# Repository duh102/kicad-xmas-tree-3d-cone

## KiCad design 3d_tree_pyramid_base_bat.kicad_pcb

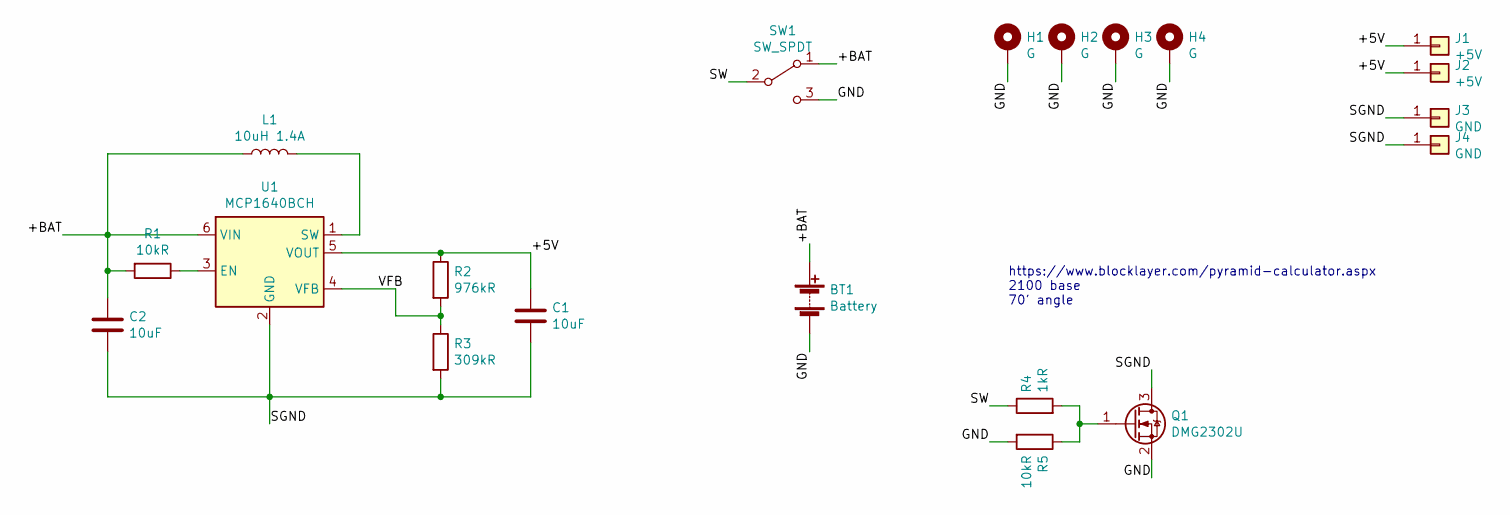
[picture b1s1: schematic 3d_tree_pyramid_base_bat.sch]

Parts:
BT1: Battery; BatteryHolder_Keystone_2479_3xAAA_noscrew
C1: 10uF; C_0805_2012Metric
C2: 10uF; C_0603_1608Metric
H1, H2, H3, H4: G; MountingHole_3.2mm_M3_DIN965_Pad
J1, J2: +5V; TestPoint_Pad_D2.0mm
J3, J4: GND; TestPoint_Pad_D2.0mm
L1: 10uH 1.4A; L_Taiyo-Yuden_NR-40xx
Q1: DMG2302U; SOT-23
R1, R5: 10kR; R_0805_2012Metric
R2: 976kR; R_0805_2012Metric
R3: 309kR; R_0805_2012Metric
R4: 1kR; R_0805_2012Metric
SW1: SW_SPDT; SW_Slide_1P2T_CK_OS102011MS2Q
U1: MCP1640BCH; SOT-23-6

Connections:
/+5V: C1.1, J1.1, J2.1, R2.1, U1.5 (VOUT)
/+BAT: BT1.1 (+), C2.1, L1.1, R1.2, SW1.1 (A), U1.6 (VIN)
/GND: BT1.2 (-), H1.1, H2.1, H3.1, H4.1, Q1.2 (S), R5.2, SW1.3 (C)
/SGND: C1.2, C2.2, J3.1, J4.1, Q1.3 (D), R3.2, U1.2 (GND)
/SW: R4.1, SW1.2 (B)
/VFB: R2.2, R3.1, U1.4 (VFB)
unnamed: L1.2, U1.1 (SW)
unnamed: Q1.1 (G), R4.2, R5.1
unnamed: R1.1, U1.3 (EN)

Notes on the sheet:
https://www.blocklayer.com/pyramid-calculator.aspx 2100 base 70' angle

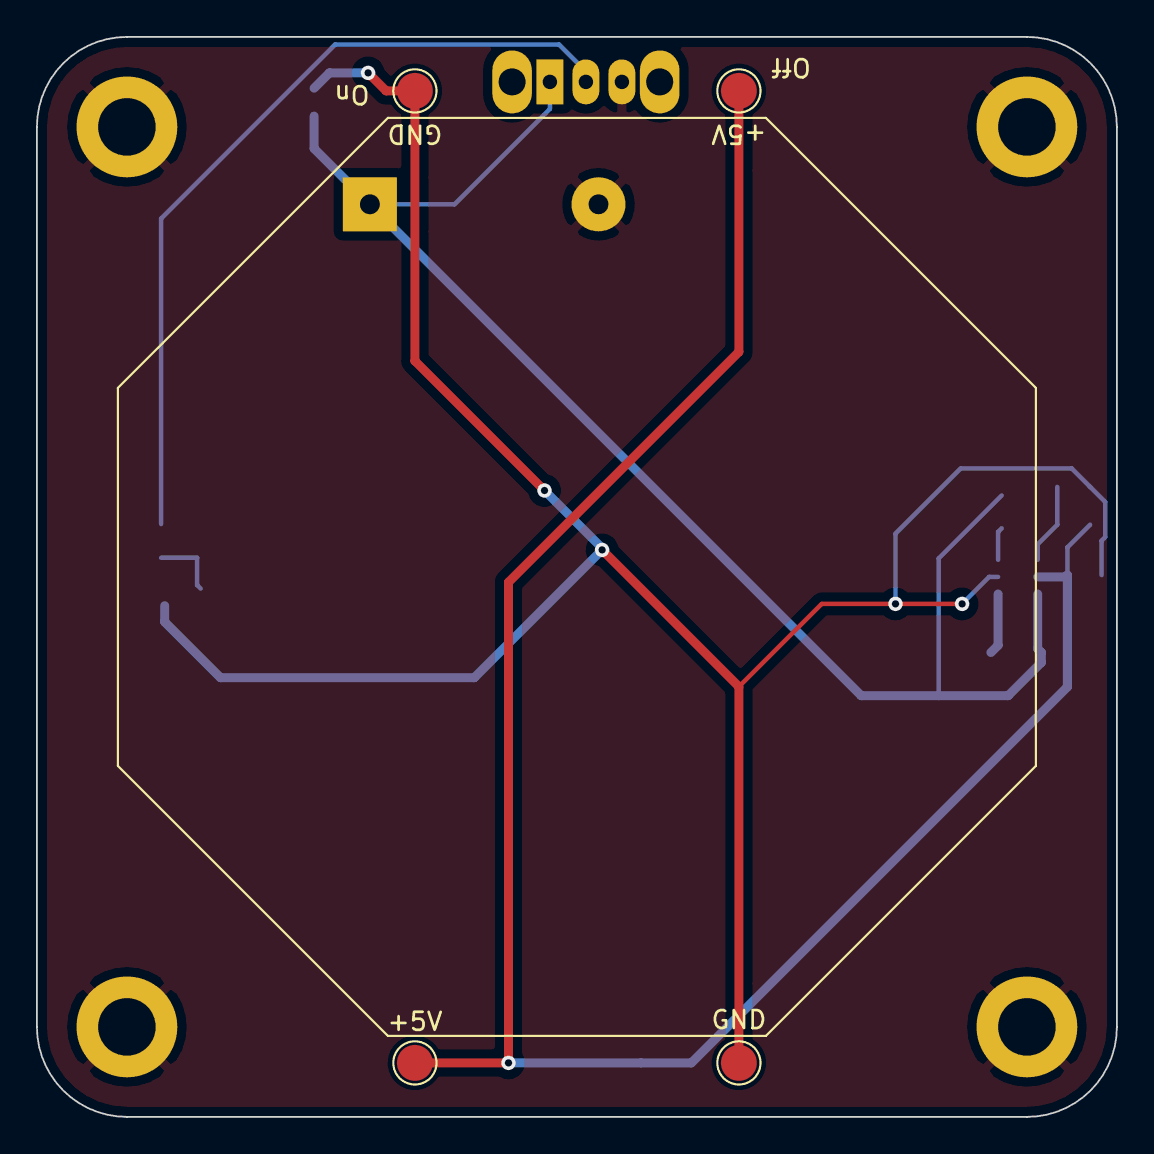
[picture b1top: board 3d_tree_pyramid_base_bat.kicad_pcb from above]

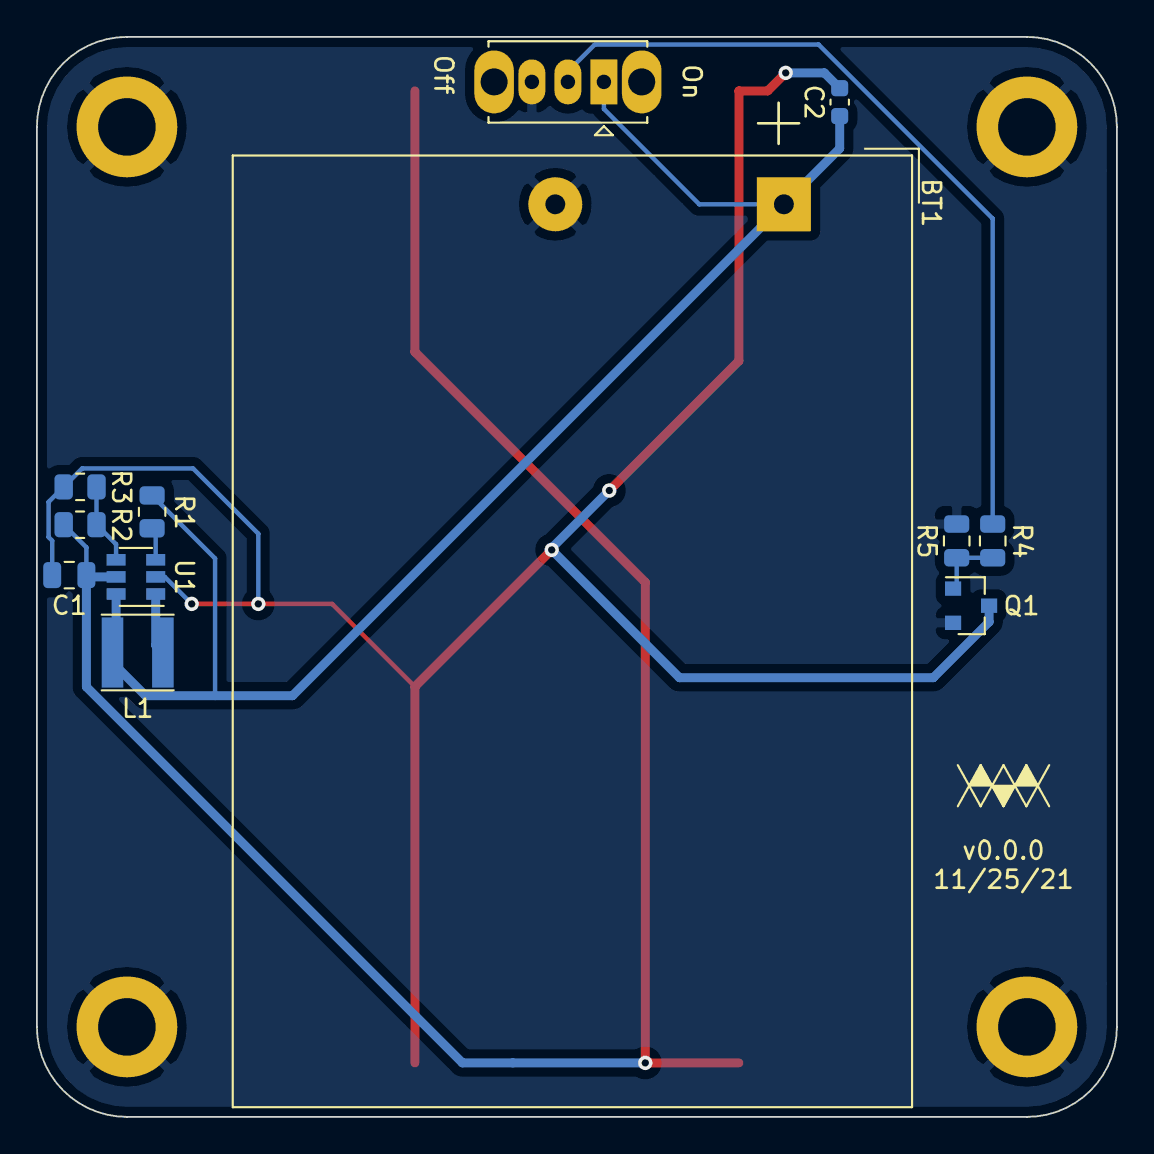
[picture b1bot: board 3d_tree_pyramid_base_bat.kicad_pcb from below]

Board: 2 copper layers, 60.0 x 60.0 mm, 20 parts (12 on the bottom side), 9 nets.

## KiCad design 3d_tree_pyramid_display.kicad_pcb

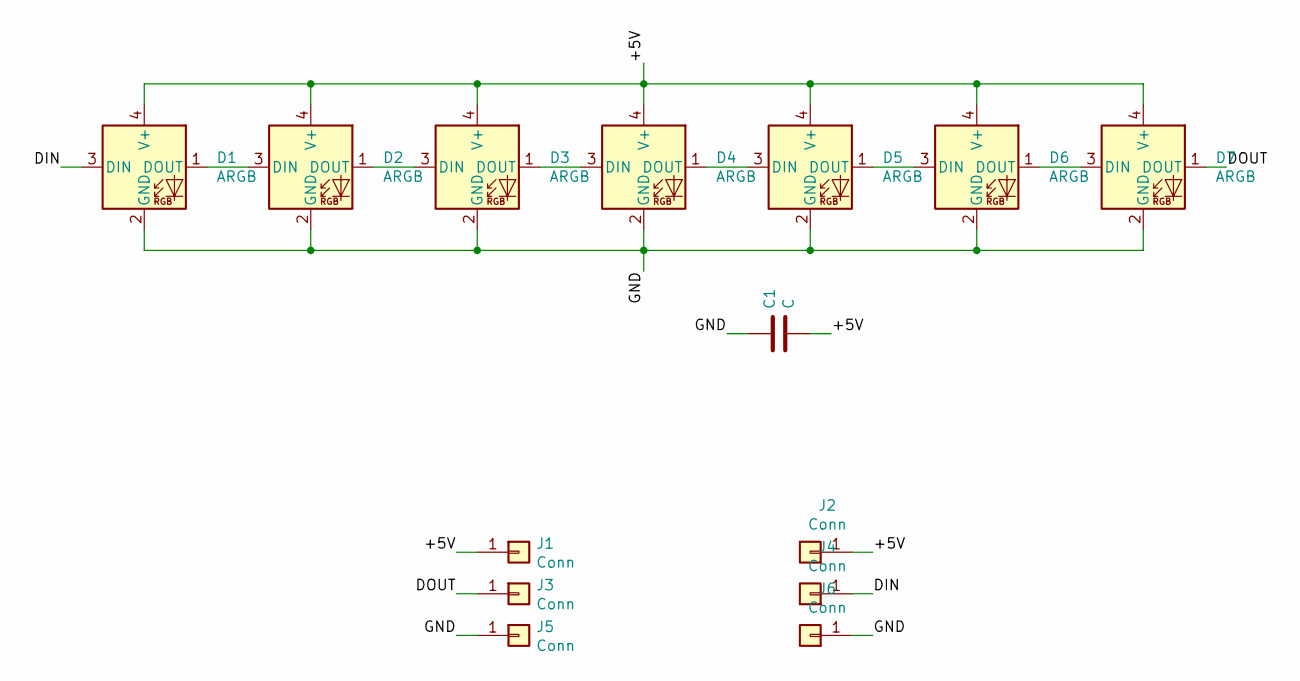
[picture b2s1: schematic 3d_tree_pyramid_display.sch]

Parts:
C1: C; C_0603_1608Metric
D1, D2, D3, D4, D5, D6, D7: ARGB; LED_SK6805_PLCC4_1.5x1.5mm_P0.65mm
J1, J2, J3, J4, J5, J6: Conn; TestPoint_Pad_D2.0mm

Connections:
/+5V: C1.2, D1.4 (V+), D2.4 (V+), D3.4 (V+), D4.4 (V+), D5.4 (V+), D6.4 (V+), D7.4 (V+), J1.1, J2.1
/DIN: D1.3 (DIN), J4.1
/DOUT: D7.1 (DOUT), J3.1
/GND: C1.1, D1.2 (GND), D2.2 (GND), D3.2 (GND), D4.2 (GND), D5.2 (GND), D6.2 (GND), D7.2 (GND), J5.1, J6.1
unnamed: D1.1 (DOUT), D2.3 (DIN)
unnamed: D2.1 (DOUT), D3.3 (DIN)
unnamed: D3.1 (DOUT), D4.3 (DIN)
unnamed: D4.1 (DOUT), D5.3 (DIN)
unnamed: D5.1 (DOUT), D6.3 (DIN)
unnamed: D6.1 (DOUT), D7.3 (DIN)

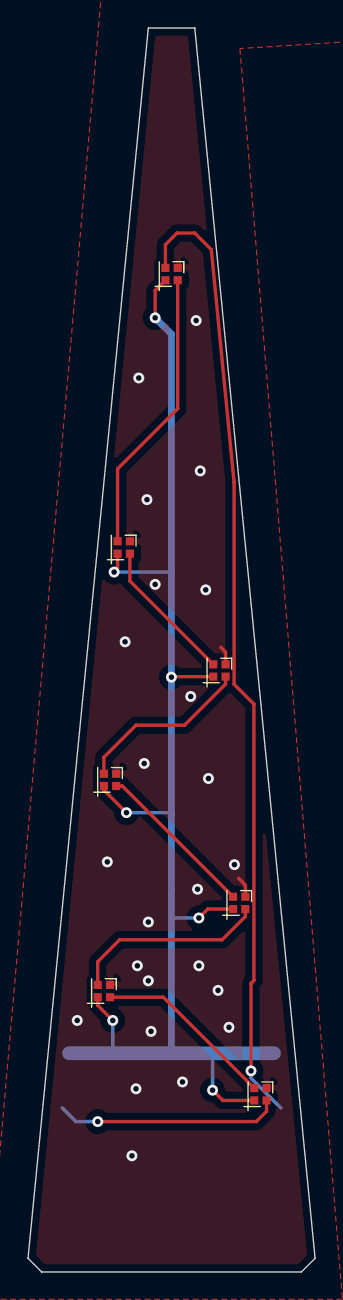
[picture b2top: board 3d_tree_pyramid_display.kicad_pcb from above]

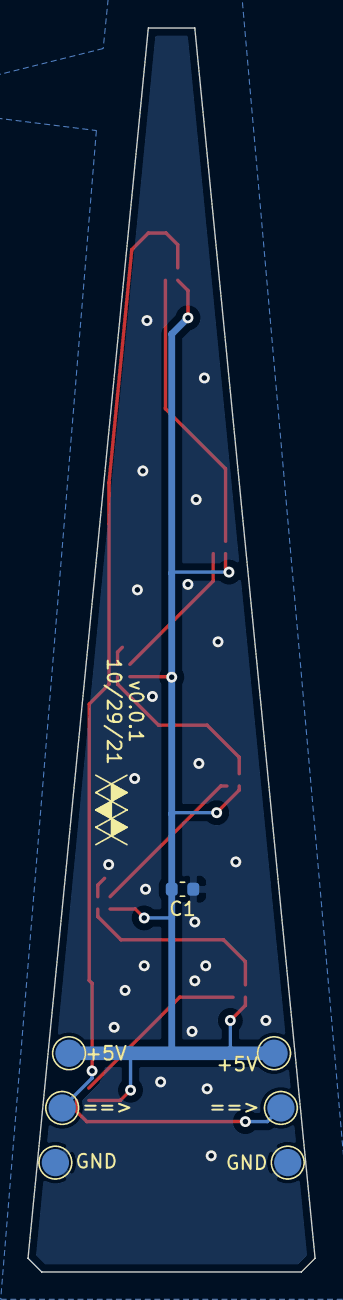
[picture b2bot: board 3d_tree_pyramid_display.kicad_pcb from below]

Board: 2 copper layers, 21.0 x 91.0 mm, 14 parts (7 on the bottom side), 10 nets.

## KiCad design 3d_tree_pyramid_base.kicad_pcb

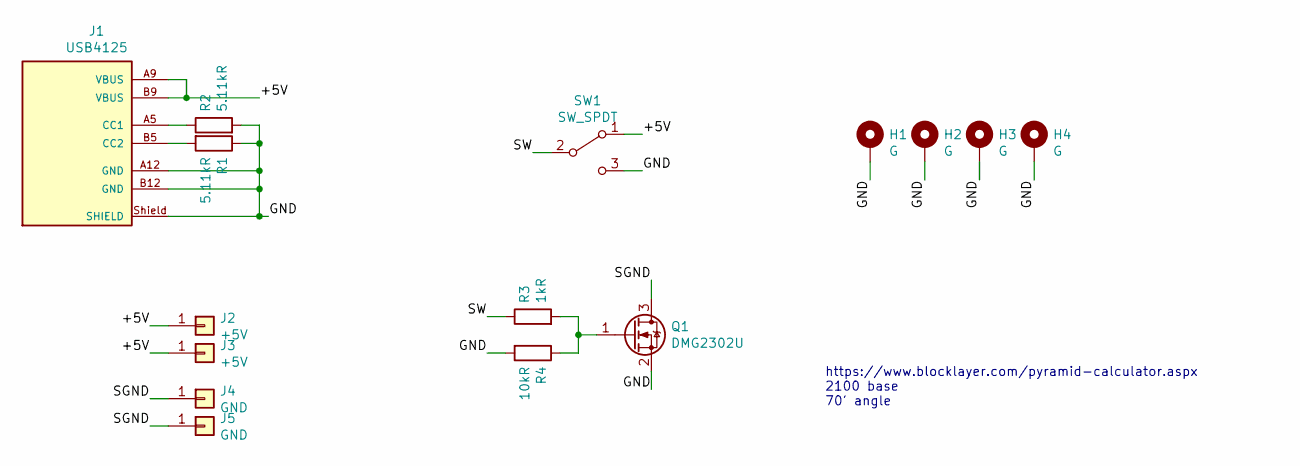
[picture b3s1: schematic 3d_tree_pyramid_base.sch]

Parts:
H1, H2, H3, H4: G; MountingHole_3.2mm_M3_DIN965_Pad
J1: USB4125; GCT_USB4125-GF-A_REVA2
J2, J3: +5V; TestPoint_Pad_D2.0mm
J4, J5: GND; TestPoint_Pad_D2.0mm
Q1: DMG2302U; SOT-23
R1, R2: 5.11kR; R_0805_2012Metric
R3: 1kR; R_0805_2012Metric
R4: 10kR; R_0805_2012Metric
SW1: SW_SPDT; SW_Slide_1P2T_CK_OS102011MS2Q

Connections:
/+5V: J1.A9 (VBUS), J1.B9 (VBUS), J2.1, J3.1, SW1.1 (A)
/GND: H1.1, H2.1, H3.1, H4.1, J1.A12 (GND), J1.B12 (GND), J1.Shield (SHIELD), Q1.2 (S), R1.1, R2.2, R4.2, SW1.3 (C)
/SGND: J4.1, J5.1, Q1.3 (D)
/SW: R3.1, SW1.2 (B)
unnamed: J1.A5 (CC1), R2.1
unnamed: J1.B5 (CC2), R1.2
unnamed: Q1.1 (G), R3.2, R4.1

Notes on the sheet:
https://www.blocklayer.com/pyramid-calculator.aspx 2100 base 70' angle

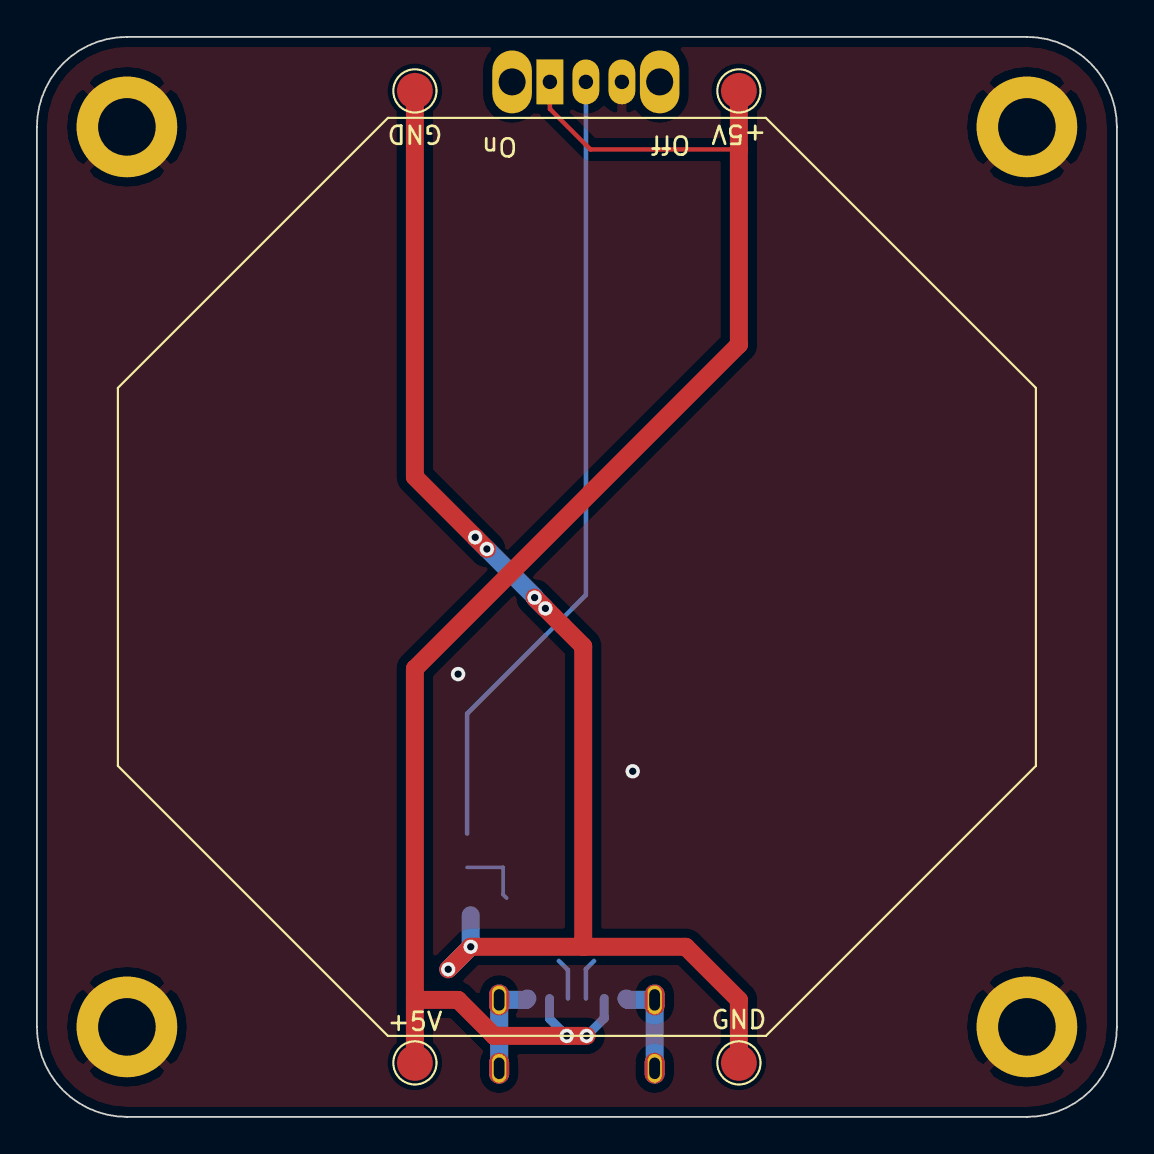
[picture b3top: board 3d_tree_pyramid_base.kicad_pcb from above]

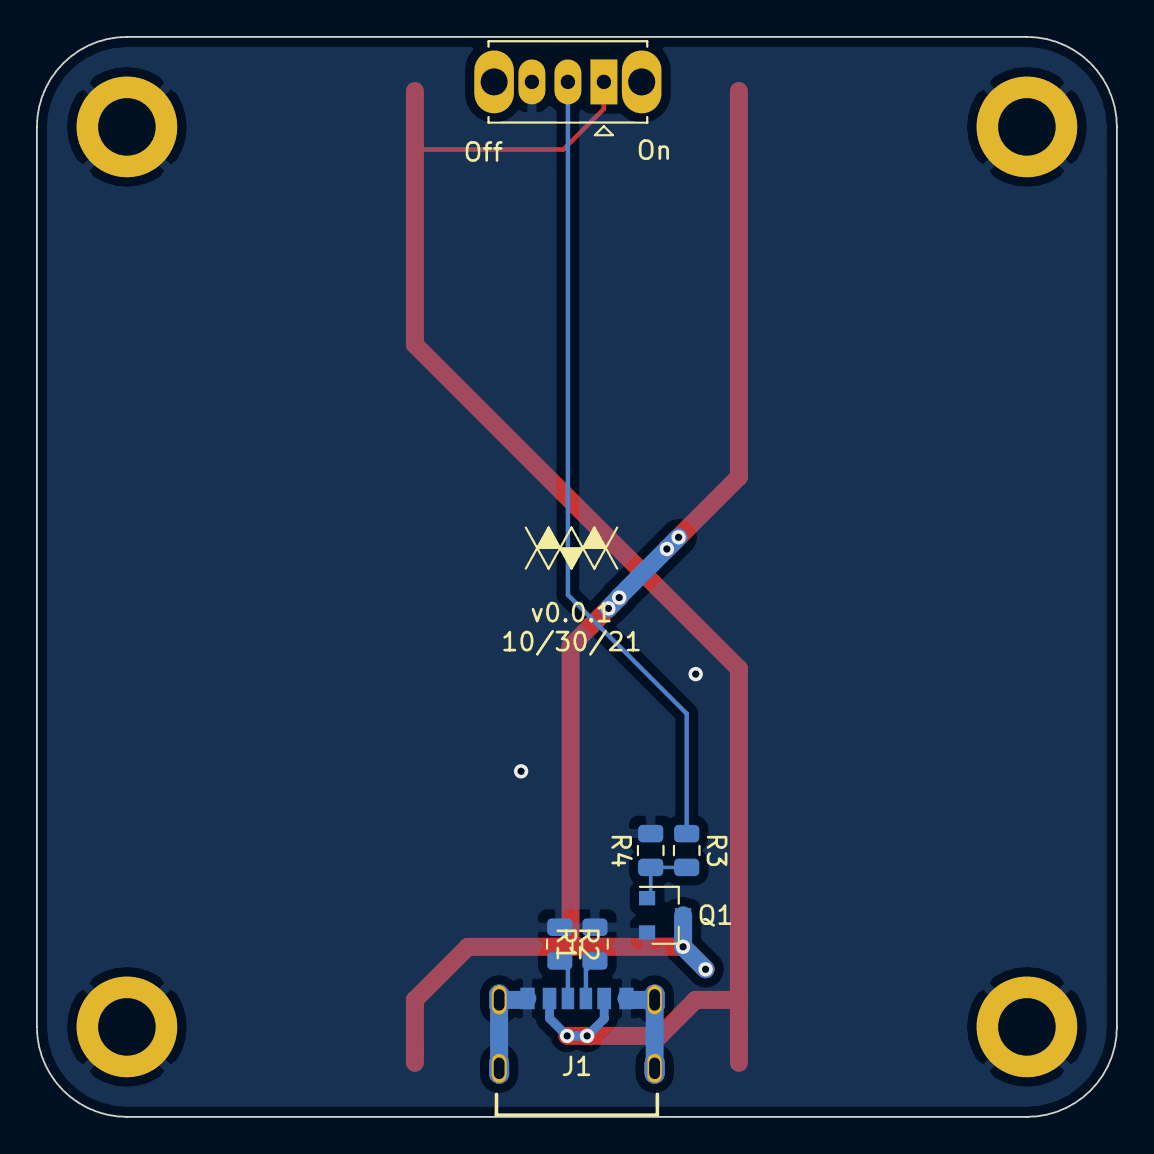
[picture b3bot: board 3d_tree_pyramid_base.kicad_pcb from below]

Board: 2 copper layers, 60.0 x 60.0 mm, 15 parts (7 on the bottom side), 7 nets.

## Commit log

2021-11-20 Update to taller cone
2021-11-27 Add battery base
